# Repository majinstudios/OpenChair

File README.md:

# OpenChair

With OpenChair we want to create the first wheelchair development platform in which users can code or design the adaptations necessary to fit their needs.

In order to do so, we modified a manual wheelchair to convert it into an electric one, designed highly customizable armrests and developed a controller board with BLE to allow users to build and control the wheelchair in the manner that best suits them.

For further information and build instructions, please check [this page](https://hackaday.io/project/13347-openchair).

Licenses
---------
Software: GPL v3
Mechanical: Creative Commons Attribution-ShareAlike 4.0 International (CC BY-SA 4.0)

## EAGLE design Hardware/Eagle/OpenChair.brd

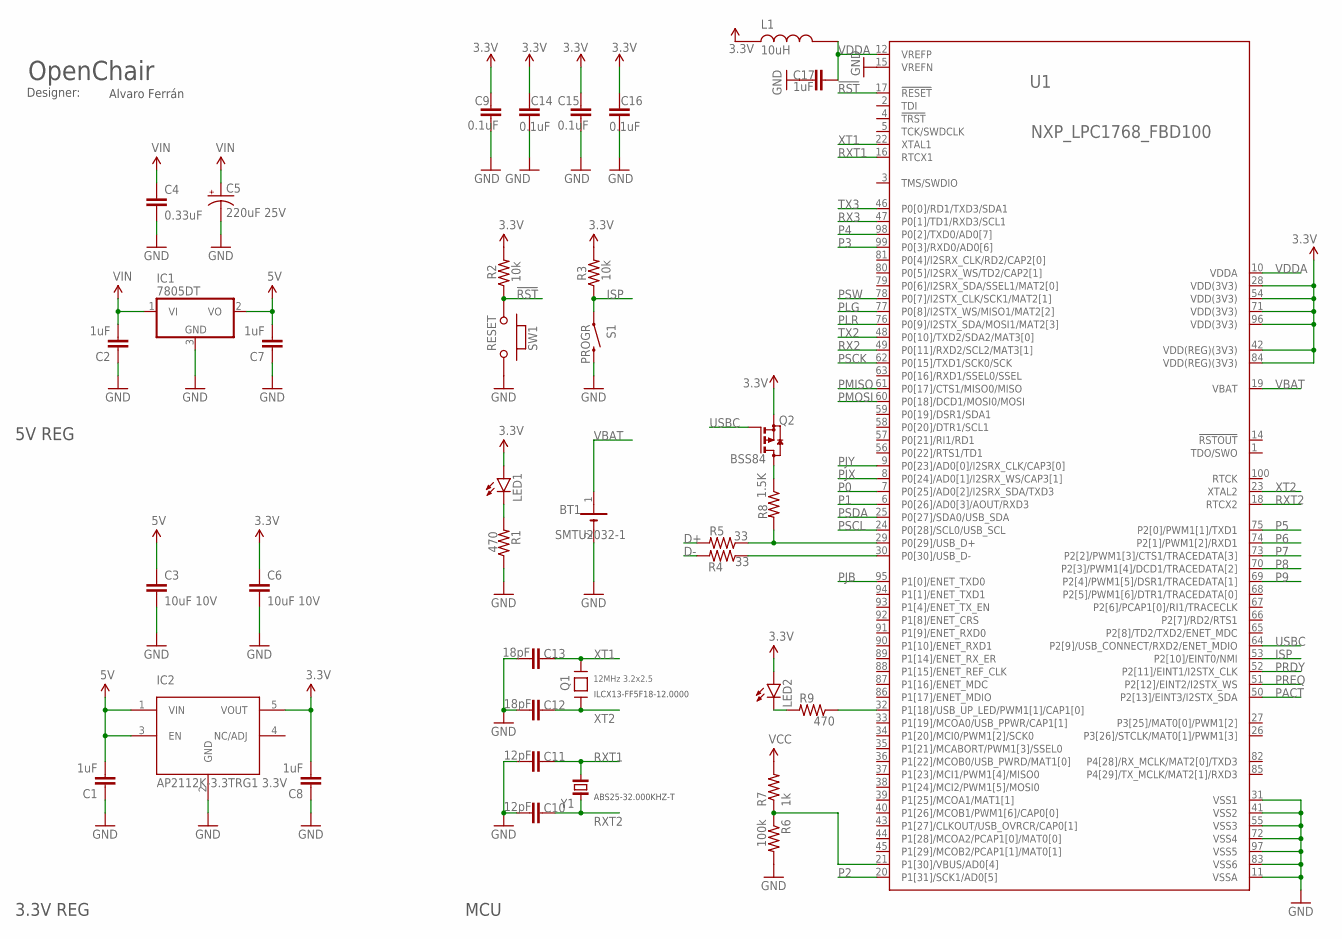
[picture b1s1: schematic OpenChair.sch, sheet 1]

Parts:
BT1: SMTU2032-1; RENATA_SMTU2032-1
C1, C2, C7, C8, C17: 1uF; 0603-CAP
C3, C6: 10uF 10V; 0603-CAP
C4: 0.33uF; 0805
C5: 220uF 25V; CPOL-RADIAL-100UF-25V
C9, C14, C15, C16: 0.1uF; 0402-CAP
C10, C11: 12pF; 0402-CAP
C12, C13: 18pF; 0402-CAP
IC1: 7805DT; TO252
IC2: AP2112K-3.3TRG1 3.3V; SOT23-5
L1: 10uH; L0603
LED1, LED2: LED0603; LED-0603
Q1: 12MHz 3.2x2.5; CRYSTAL_3.2X2.5
Q2: BSS84; SOT23
R1, R9: 470; 0402-RES
R2, R3: 10k; 0402-RES
R4, R5: 33; 0402-RES
R6: 100k; 0402-RES
R7: 1k; 0402-RES
R8: 1.5K; 0402-RES
S1: PROGR; TACTILE-PTH-SIDEEZ
SW1: RESET; 157SW
U1: NXP_LPC1768_FBD100; QFP50P1600X1600X160-100N
Y1: ABS25

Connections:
3.3V: C6.1, C8.2, C9.1, C14.1, C15.1, C16.1, IC2.5 (VOUT), L1.P$1, LED1.A, LED2.A, Q2.2 (S), R2.2, R3.2, U1.28 (VDD(3V3)), U1.42 (VDD(REG)(3V3)), U1.54 (VDD(3V3)), U1.71 (VDD(3V3)), U1.84 (VDD(REG)(3V3)), U1.96 (VDD(3V3)); also elsewhere on the board
5V: C1.2, C3.1, C7.2, IC1.2 (VO), IC2.1 (VIN), IC2.3 (EN); also elsewhere on the board
!RST: R2.1, SW1.1, U1.17 (!RESET)
D+: R5.2; also elsewhere on the board
D-: R4.2; also elsewhere on the board
GND: BT1.2 (-), C1.1, C2.1, C3.2, C4.2, C5.2 (-), C6.2, C7.1, C8.1, C9.2, C10.2, C11.2, C12.2, C13.2, C14.2, C15.2, C16.2, C17.1, IC1.3 (GND), IC2.2 (GND), R1.1, R6.2, S1.2, SW1.2, U1.11 (VSSA), U1.15 (VREFN), U1.31 (VSS1), U1.41 (VSS2), U1.55 (VSS3), U1.72 (VSS4), U1.83 (VSS6), U1.97 (VSS5); also elsewhere on the board
ISP: R3.1, S1.1, U1.53 (P2[10]/EINT0/NMI)
unnamed: LED1.C, R1.2
unnamed: R6.1, R7.1, U1.21 (P1[30]/VBUS/AD0[4])
unnamed: R5.1, R8.2, U1.29 (P0[29]/USB_D+)
unnamed: R9.1, U1.32 (P1[18]/USB_UP_LED/PWM1[1]/CAP1[0])
unnamed: LED2.C, R9.2
unnamed: R4.1, U1.30 (P0[30]/USB_D-)
unnamed: Q2.3 (D), R8.1
P0: U1.7 (P0[25]/AD0[2]/I2SRX_SDA/TXD3); also elsewhere on the board
P1: U1.6 (P0[26]/AD0[3]/AOUT/RXD3); also elsewhere on the board
P2: U1.20 (P1[31]/SCK1/AD0[5]); also elsewhere on the board
P3: U1.99 (P0[3]/RXD0/AD0[6]); also elsewhere on the board
P4: U1.98 (P0[2]/TXD0/AD0[7]); also elsewhere on the board
P5: U1.75 (P2[0]/PWM1[1]/TXD1); also elsewhere on the board
P6: U1.74 (P2[1]/PWM1[2]/RXD1); also elsewhere on the board
P7: U1.73 (P2[2]/PWM1[3]/CTS1/TRACEDATA[3]); also elsewhere on the board
P8: U1.70 (P2[3]/PWM1[4]/DCD1/TRACEDATA[2]); also elsewhere on the board
P9: U1.69 (P2[4]/PWM1[5]/DSR1/TRACEDATA[1]); also elsewhere on the board
PACT: U1.50 (P2[13]/EINT3/I2STX_SDA); also elsewhere on the board
PJB: U1.95 (P1[0]/ENET_TXD0); also elsewhere on the board
PJX: U1.8 (P0[24]/AD0[1]/I2SRX_WS/CAP3[1]); also elsewhere on the board
PJY: U1.9 (P0[23]/AD0[0]/I2SRX_CLK/CAP3[0]); also elsewhere on the board
PLG: U1.77 (P0[8]/I2STX_WS/MISO1/MAT2[2]); also elsewhere on the board
PLR: U1.76 (P0[9]/I2STX_SDA/MOSI1/MAT2[3]); also elsewhere on the board
PMISO: U1.61 (P0[17]/CTS1/MISO0/MISO); also elsewhere on the board
PMOSI: U1.60 (P0[18]/DCD1/MOSI0/MOSI); also elsewhere on the board
PRDY: U1.52 (P2[11]/EINT1/I2STX_CLK); also elsewhere on the board
PREQ: U1.51 (P2[12]/EINT2/I2STX_WS); also elsewhere on the board
PSCK: U1.62 (P0[15]/TXD1/SCK0/SCK); also elsewhere on the board
PSCL: U1.24 (P0[28]/SCL0/USB_SCL); also elsewhere on the board
PSDA: U1.25 (P0[27]/SDA0/USB_SDA); also elsewhere on the board
PSW: U1.78 (P0[7]/I2STX_CLK/SCK1/MAT2[1]); also elsewhere on the board
RX2: U1.49 (P0[11]/RXD2/SCL2/MAT3[1]); also elsewhere on the board
RX3: U1.47 (P0[1]/TD1/RXD3/SCL1)
RXT1: C11.1, U1.16 (RTCX1), Y1.1
RXT2: C10.1, U1.18 (RTCX2), Y1.4 (2)
TX2: U1.48 (P0[10]/TXD2/SDA2/MAT3[0]); also elsewhere on the board
TX3: U1.46 (P0[0]/RD1/TXD3/SDA1); also elsewhere on the board
USBC: Q2.1 (G), U1.64 (P2[9]/USB_CONNECT/RXD2/ENET_MDIO)
VBAT: BT1.1 (+), U1.19 (VBAT)
VCC: R7.2; also elsewhere on the board
VDDA: C17.2, L1.P$2, U1.10 (VDDA), U1.12 (VREFP)
VIN: C2.2, C4.1, C5.1 (+), IC1.1 (VI); also elsewhere on the board
XT1: C13.1, Q1.3, U1.22 (XTAL1)
XT2: C12.1, Q1.1, U1.23 (XTAL2)

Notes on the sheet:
3.3V REG
OpenChair
Designer:
Alvaro Ferrán
5V REG
MCU
ILCX13-FF5F18-12.0000
ABS25-32.000KHZ-T

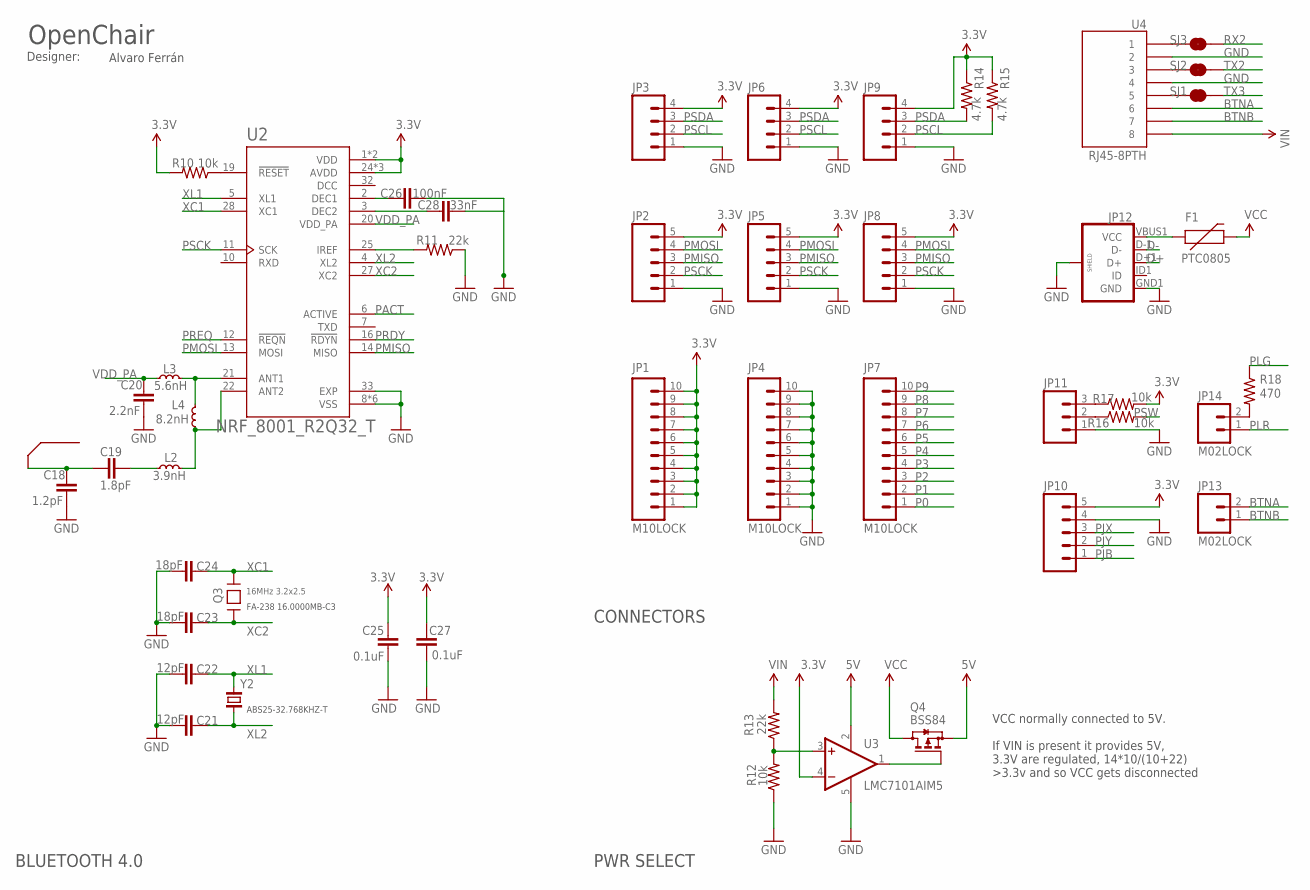
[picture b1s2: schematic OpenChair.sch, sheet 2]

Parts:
ANT1: NRF_ANTENNA
C18: 1.2pF; 0402-CAP
C19: 1.8pF; 0402-CAP
C20: 2.2nF; 0402-CAP
C21, C22: 12pF; 0402-CAP
C23, C24: 18pF; 0402-CAP
C25, C27: 0.1uF; 0402-CAP
C26: 100nF; 0402-CAP
C28: 33nF; 0402-CAP
F1: PTC0805; 0805
JP1, JP4, JP7: M10LOCK; 1X10_LOCK
JP2, JP5, JP8, JP10: M05LOCK; 1X05_LOCK
JP3, JP6, JP9: M04LOCK; 1X04_LOCK
JP11: M03LOCK; 1X03_LOCK
JP12: USB_MICROB_PLUGCONN-11752; USB-B-MICRO-SMD_V03
JP13, JP14: M02LOCK; 1X02_LOCK
L2: 3.9nH; 0402
L3: 5.6nH; 0402
L4: 8.2nH; 0402
Q3: 16MHz 3.2x2.5; CRYSTAL_3.2X2.5
Q4: BSS84; SOT23
R10, R12, R16, R17: 10k; 0402-RES
R11, R13: 22k; 0402-RES
R14, R15: 4.7k; 0402-RES
R18: 470; 0402-RES
SJ1, SJ2, SJ3: JUMPER-PAD-2-NC_BY_TRACE; PAD-JUMPER-2-NC_BY_TRACE_YES_SILK
U2: NRF_8001_R2Q32_T; QFN50P500X500X90-33N
U3: LMC7101AIM5; SOT23-5
U4: RJ45-8PTH; RJ45-8
Y2: ABS25-32.768kHz; ABS25

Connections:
3.3V: C25.1, C27.1, JP1.1, JP1.2, JP1.3, JP1.4, JP1.5, JP1.6, JP1.7, JP1.8, JP1.9, JP1.10, JP2.5, JP3.4, JP5.5, JP6.4, JP8.5, JP9.4, JP10.5, R10.2, R14.1, R15.1, R17.2, U2.1 (VDD), U2.9 (VDD), U2.24 (AVDD), U2.26 (AVDD), U2.29 (AVDD), U3.4 (-IN); also elsewhere on the board
5V: Q4.2 (S), U3.2 (V+); also elsewhere on the board
BTNA: JP13.2, U4.6
BTNB: JP13.1, U4.7
D+: JP12.D+1 (D+); also elsewhere on the board
D-: JP12.D-1 (D-); also elsewhere on the board
DCC: U2.32 (DCC)
GND: C18.2, C20.2, C21.2, C22.2, C23.2, C24.2, C25.2, C26.1, C27.2, C28.1, JP2.1, JP3.1, JP4.1, JP4.2, JP4.3, JP4.4, JP4.5, JP4.6, JP4.7, JP4.8, JP4.9, JP4.10, JP5.1, JP6.1, JP8.1, JP9.1, JP10.4, JP11.1, JP12.GND1 (GND), JP12.SHIELD1 (SHIELD), JP12.SHIELD2 (SHIELD), JP12.SHIELD3 (SHIELD), R11.1, R12.1, U2.8 (VSS), U2.17 (VSS), U2.18 (VSS), U2.23 (VSS), U2.30 (VSS), U2.31 (VSS), U2.33 (EXP), U3.5 (V-), U4.2, U4.4; also elsewhere on the board
unnamed: JP14.2, R18.2
unnamed: SJ3.1, U4.1
unnamed: SJ2.1, U4.3
unnamed: SJ1.1, U4.5
unnamed: F1.1, JP12.VBUS1 (VCC)
unnamed: JP11.2, R16.1
unnamed: JP11.3, R17.1
unnamed: Q4.1 (G), U3.1 (OUT)
unnamed: R12.2, R13.1, U3.3 (+IN)
unnamed: R11.2, U2.25 (IREF)
unnamed: C26.2, U2.2 (DEC1)
unnamed: C28.2, U2.3 (DEC2)
unnamed: R10.1, U2.19 (!RESET)
unnamed: L2.2, L4.1, U2.22 (ANT2)
unnamed: L3.2, L4.2, U2.21 (ANT1)
unnamed: C19.1, L2.1
unnamed: ANT1.P$1, C18.1, C19.2
P0: JP7.1; also elsewhere on the board
P1: JP7.2; also elsewhere on the board
P2: JP7.3; also elsewhere on the board
P3: JP7.4; also elsewhere on the board
P4: JP7.5; also elsewhere on the board
P5: JP7.6; also elsewhere on the board
P6: JP7.7; also elsewhere on the board
P7: JP7.8; also elsewhere on the board
P8: JP7.9; also elsewhere on the board
P9: JP7.10; also elsewhere on the board
PACT: U2.6 (ACTIVE); also elsewhere on the board
PJB: JP10.1; also elsewhere on the board
PJX: JP10.3; also elsewhere on the board
PJY: JP10.2; also elsewhere on the board
PLG: R18.1; also elsewhere on the board
PLR: JP14.1; also elsewhere on the board
PMISO: JP2.3, JP5.3, JP8.3, U2.14 (MISO); also elsewhere on the board
PMOSI: JP2.4, JP5.4, JP8.4, U2.13 (MOSI); also elsewhere on the board
PRDY: U2.16 (!RDYN); also elsewhere on the board
PREQ: U2.12 (!REQN); also elsewhere on the board
PSCK: JP2.2, JP5.2, JP8.2, U2.11 (SCK); also elsewhere on the board
PSCL: JP3.2, JP6.2, JP9.2, R15.2; also elsewhere on the board
PSDA: JP3.3, JP6.3, JP9.3, R14.2; also elsewhere on the board
PSW: R16.2; also elsewhere on the board
RX2: SJ3.2; also elsewhere on the board
TX2: SJ2.2; also elsewhere on the board
TX3: SJ1.2; also elsewhere on the board
VCC: F1.2, Q4.3 (D); also elsewhere on the board
VDD_PA: C20.1, L3.1, U2.20 (VDD_PA)
VIN: R13.2, U4.8; also elsewhere on the board
XC1: C24.1, Q3.3, U2.28 (XC1)
XC2: C23.1, Q3.1, U2.27 (XC2)
XL1: C22.1, U2.5 (XL1), Y2.4 (2)
XL2: C21.1, U2.4 (XL2), Y2.1

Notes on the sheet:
OpenChair
Designer:
Alvaro Ferrán
CONNECTORS
VCC normally connected to 5V. If VIN is present it provides 5V, 3.3V are regulated, 14*10/(10+22) >3.3v and so VCC gets disconnected
PWR SELECT
ABS25-32.768KHZ-T
FA-238 16.0000MB-C3
BLUETOOTH 4.0

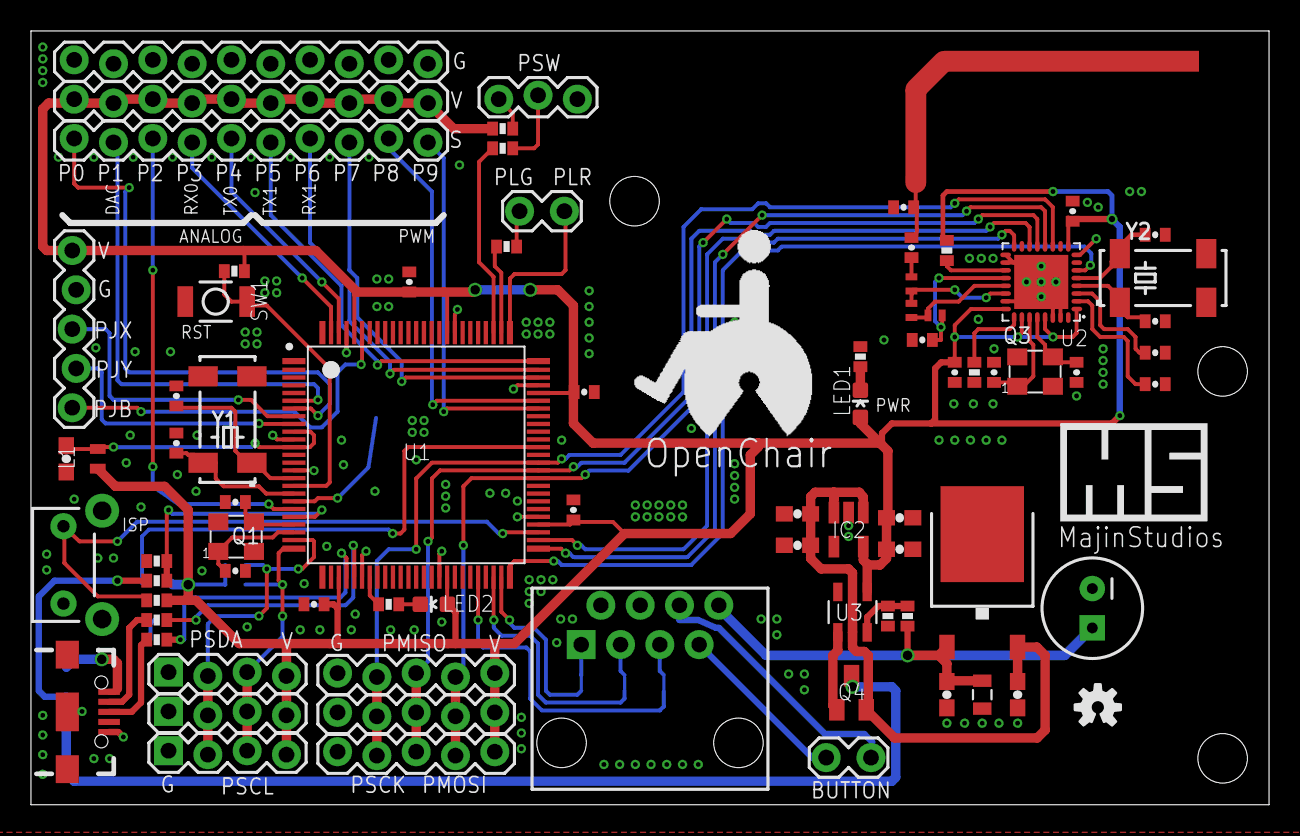
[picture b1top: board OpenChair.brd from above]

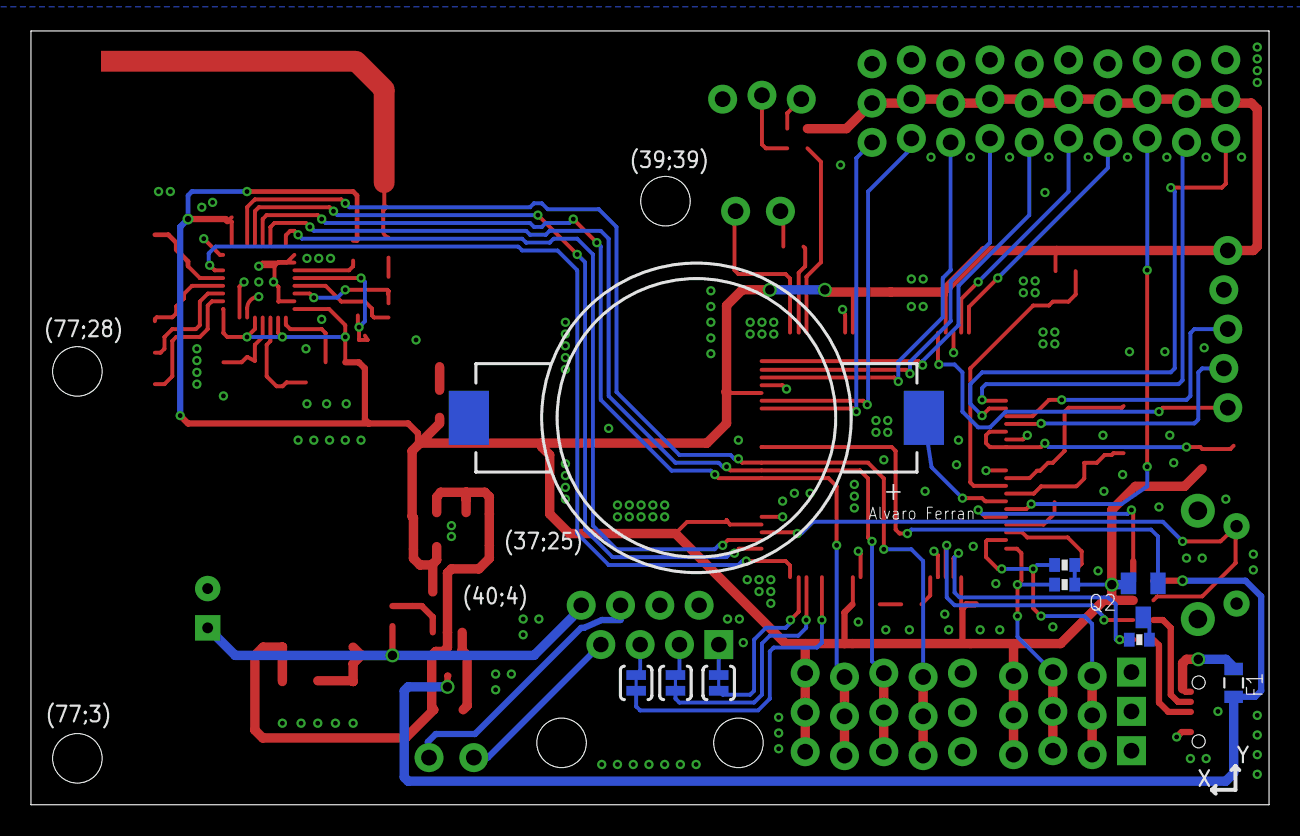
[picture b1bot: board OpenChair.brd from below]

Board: 2 copper layers, 80.0 x 50.0 mm, 89 parts (9 on the bottom side), 74 nets.

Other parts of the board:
U$1: MAJINSTUDIOS
U$2: OPENCHAIR2
U$3: OSHW-LOGO-S

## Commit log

2016-08-30 Library added
2016-08-31 Forward and backward controlled smoothly using a joystick
2016-08-31 Forward, backwards, left and right working OK
2016-08-31 Small fix in test driving move
2016-08-31 Added open chair logo
2016-09-05 Added the armrest 3D files and modular hitches for accessories
2016-09-06 New armrest version taking into account the chairs inner space. Hoverboard fastener v0.0.1
2016-09-10 Added hoverboard fastener system and improved armrest_thin features
2016-09-10 Modified to use sudden stop, modified baud rate to 26300
2016-09-10 Modified joystick control so it works with this board
2016-09-18 Changes in design, backup working demo sw
2016-09-21 OpenChair code fully working!! :)
2016-09-30 Maker faire small changes in code, design & logos
2016-09-30 Reordered Mechanical part, updated READMEs and LICENCEs and cleaned up Software part
2016-10-01 OpenChair board added
2016-10-02 Added Gerber RS274X files and updated PDF
2016-10-07 Added wood plank 3D design

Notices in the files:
parts and their libraries:
SparkFun-Passives: Licensing: Creative Commons ShareAlike 4.0 International - https://creativecommons.org/licenses/by-sa/4.0
